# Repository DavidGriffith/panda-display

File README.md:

Panda Display Panel
===================

---

The Panda Display Panel is a hardware peripheral for use with the klh10 
pdp-10 emulator.  It was originally presented by Spare Time Gizmos.  
This one replaces the parallel port interface with a USB interface.

The original Panda Display Panel page is at 
http://www.sparetimegizmos.com/Hardware/Panda.htm

**Bill of Materials**

|Connectors| |
|:----------|---|
|J1| 1 x 4 0.1" header strip|
|J2| 2 x 3 0.1" header strip|
|U1| 28-pin narrow DIP socket|
|U2| 24-pin narrow DIP socket|

|Semiconductors| |
|:--------------|---|
|U1|		ATmega8 microcontroller -- 28-pin narrow DIP|
|U2|		Maxim MAX7219 matrix digit display driver -- 24-pin narrow DIP|
|D1,D2|		1N747 3.6V zener diodes|
|BAR1-BAR4|	10 segment LED bar display -- Lite-On LTA-1000HR|
|LED1-LED4|	Standard brightness red LED 5mm -- Kingbright WP1503ID|

|Crystals| |
|:--------|---|
|Y1|		16MHz quartz crystal -- HC49/US low profile|

|Resistors| |
|:---------|---|
|R1|		2.2K 0.25W 5%|
|R2|		4.7K 0.25W 5%|
|R3,R4|		68   0.25W 5%|
|R5|		10K  0.25W 5%|

|Capacitors| |
|:----------|---|
|C1|		10uF 25V electrolytic or tantalum|
|C2,C3|		0.1uF ceramic monolithic|
|C4,C5|		22pF ceramic monolithic|

**Assembly Notes**

Pay careful attention to the fact that the chips are mounted on the rear 
of the board and most of the passives are on the front.

1.  Mount the passive components first.  Make sure the leads are trimmed 
    so they won't interfere with the chip sockets.  The polarized 
    capacitor should be laid down on its side.
2.  Wash flux residue off the rear.  The chip sockets will make this 
    more difficult later.
3.  Mount the chip sockets and the header strips on the rear
4.  Mount the LED bars and the discrete LEDs on the front.

The discrete LEDs may be pressed up against the board unless you decide 
to mount the LED bars in sockets.  If you want to do that, first mount 
sockets and install the LED bars in the sockets.  Then insert a discrete 
LED and turn the Panda Display over such that the LED bars lie flat upon 
the table.  Let the discrete LED fall against the table.  Once you're 
satisfied that the discrete LED is level with the LED bars, solder the 
discrete LED in place.  Repeat for the other discrete LEDs.

To build and install the firmware, you must have the AVR-GCC development 
environment including compiler, binutilities, and libc 
(http://www.nongnu.org/avr-libc/) and AVRDUDE
(http://www.nongnu.org/avrdude/) installed.  Most if not all current 
distributions of Linux and BSD include packages for installing these.  
You will also need an AVR programming device supported by AVRDUDE.  A 
USBtinyISP (https://www.adafruit.com/products/46) is commonly-available, 
reliable, and inexpensive.

It's a good idea to add your programmer to your system's udev rules.  
For the USBtinyISP, see https://learn.adafruit.com/usbtinyisp/avrdude

**Mounting and Use**

The Panda Display is intended to be mounted in a 5.25" external drive 
bay behind a knockout panel.  It's up to you to make this as simply or 
elaborately as you desire.  An overlay may be applied over the top to 
dress it up.

This edition of the Panda Display is powered and driven through a USB 
port.  There are two ways of going about the cabling.  If you have a 
spare USB header on your computer's motherboard, you'll need to make up 
a four-conductor cable terminated at both ends with a 1x4 0.1" female 
header socket.

If you have a regular Type-A socket inside your computer, take an 
ordinary USB cable, cut off the Type-B end, trim the jacket, and crimp 
the conductors to a 1x4 0.1" female header socket.

Finally, to make any meaningful use of the Panda Display, you will need 
a PDP-10 emulator which has been patched to make use of it.  Since 
Kenneth L. Harrenstien's klh10 pdp-10 emulator was patched by Mark 
Crispin to use the original Panda Display, I chose to modify that to use 
this new Panda Display.  Get it here: 
https://github.com/DavidGriffith/klh10.

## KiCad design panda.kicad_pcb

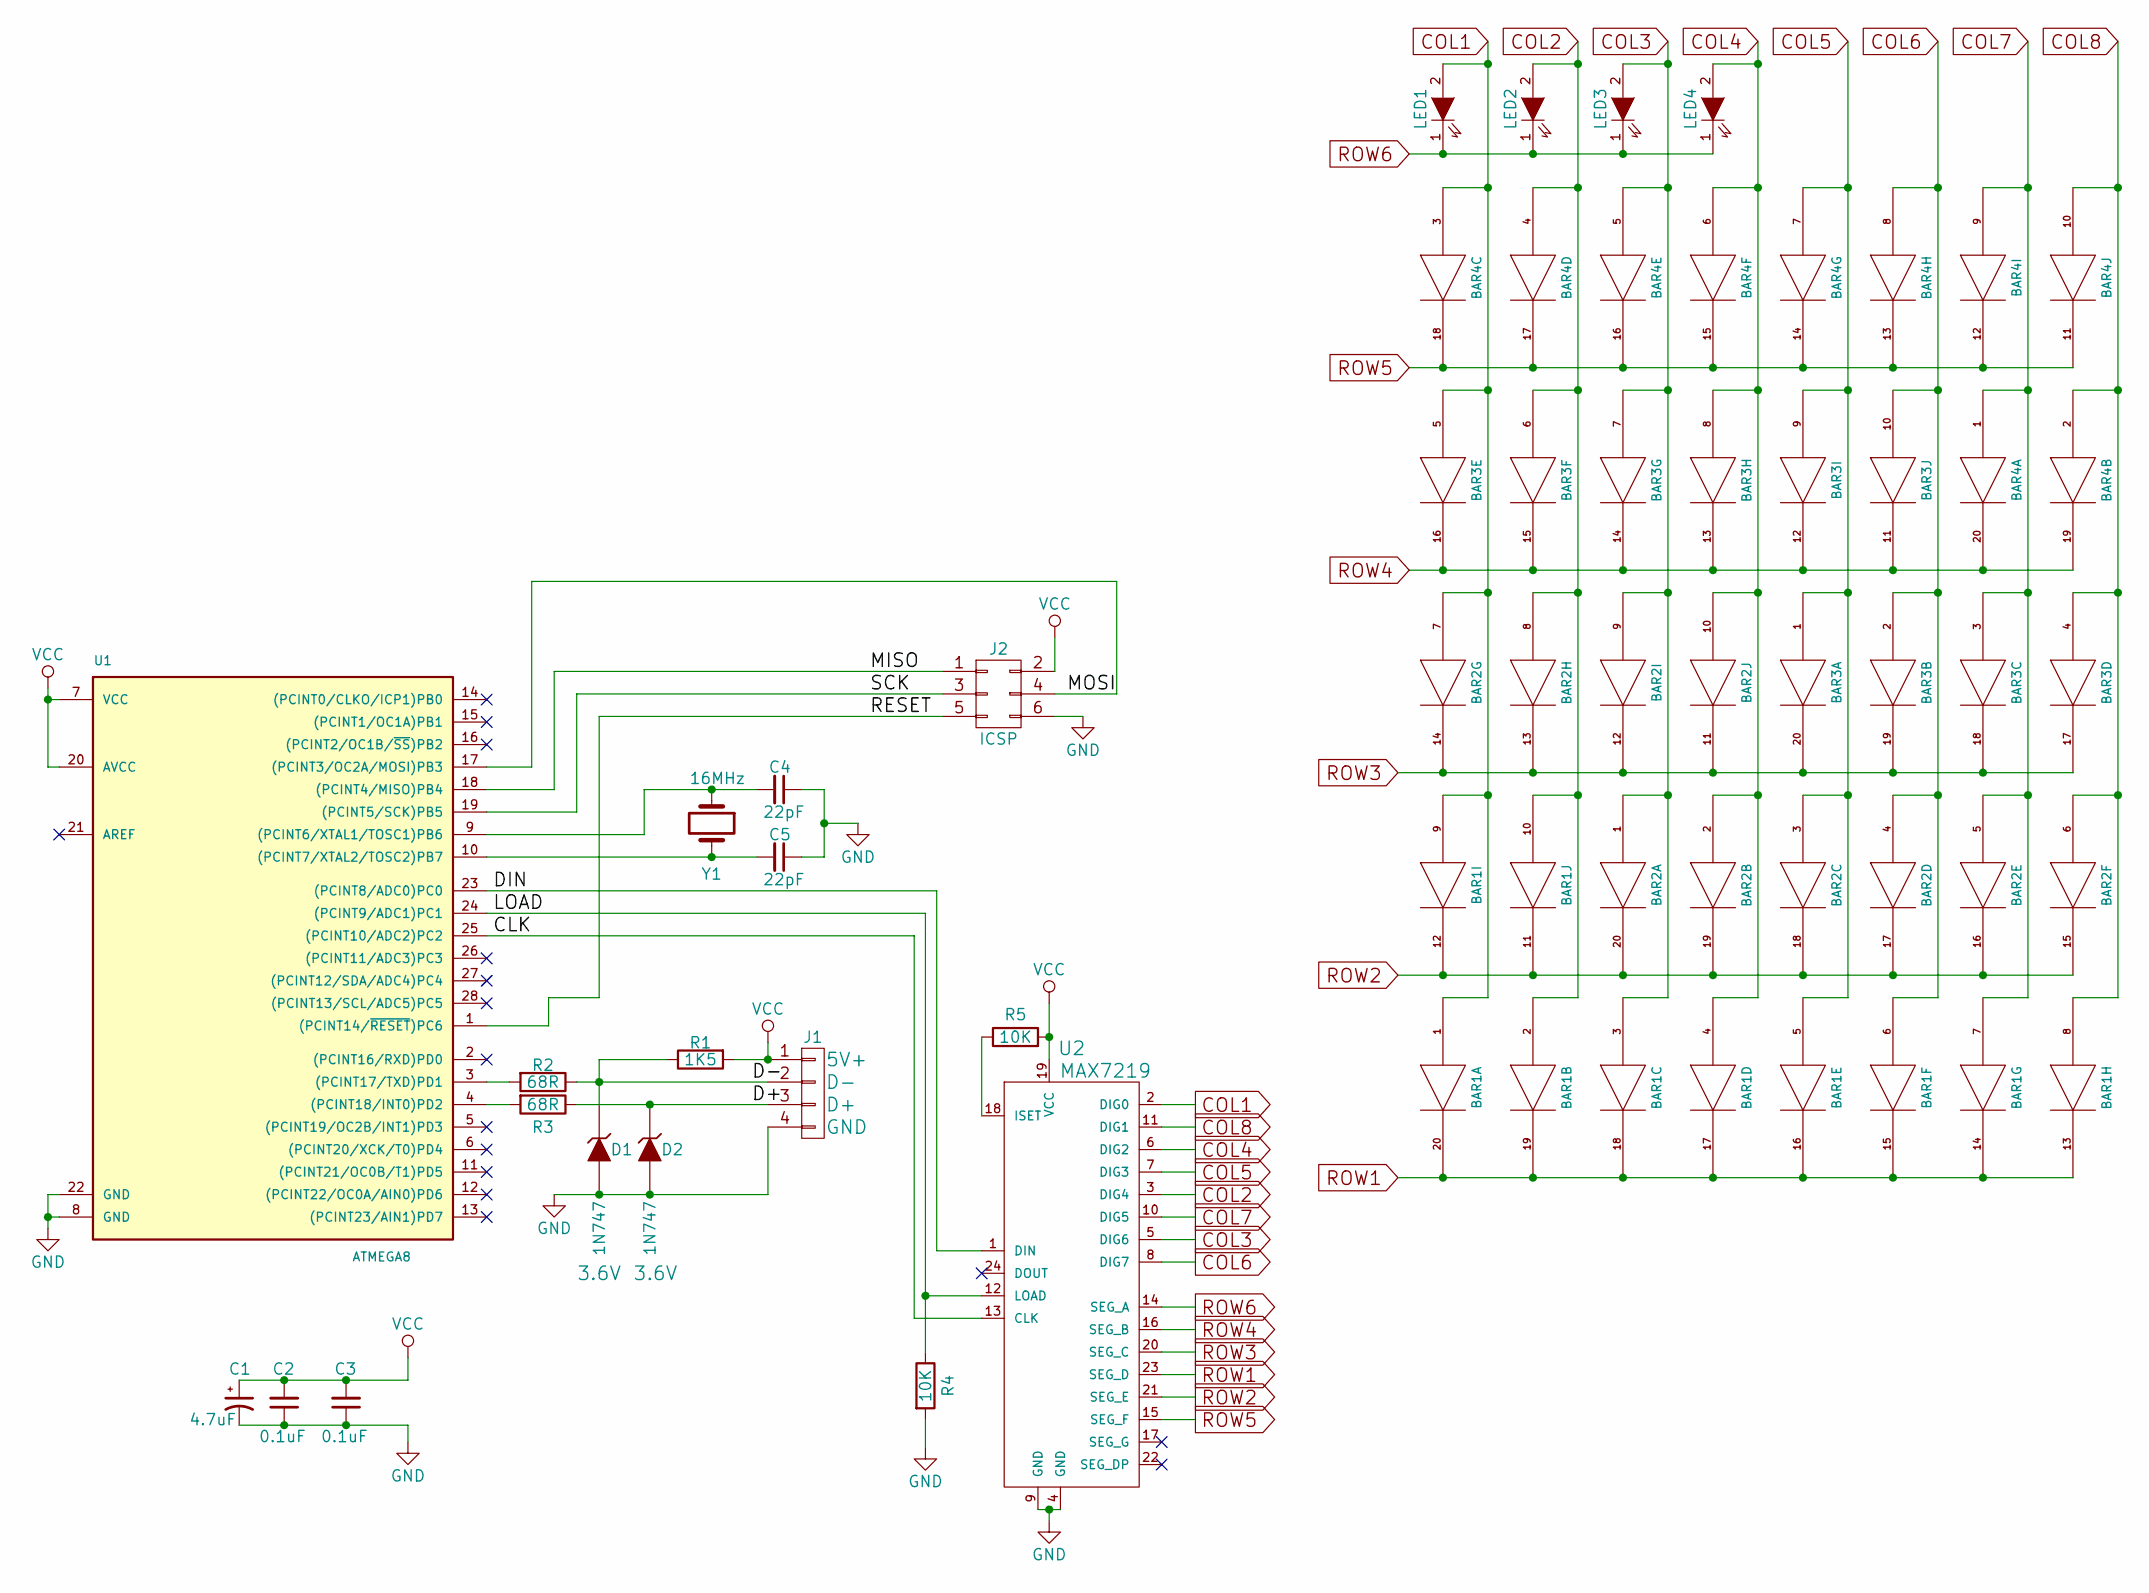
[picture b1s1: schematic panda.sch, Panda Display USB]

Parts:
BAR1, BAR2, BAR3, BAR4: DOT-BAR; DIP-20_W7.62mm
C1: 4.7uF; CP_Radial_D5.0mm_P2.50mm
C2, C3: 0.1uF; C_Disc_D3.0mm_W1.6mm_P2.50mm
C4, C5: 22pF; C_Disc_D3.0mm_W1.6mm_P2.50mm
D1, D2: 1N747; D_DO-35_SOD27_P7.62mm_Horizontal; Voltage 3.6V
J1: USB; Pin_Header_Straight_1x04_Pitch2.54mm
J2: ICSP; Pin_Header_Straight_2x03_Pitch2.54mm
LED1, LED2, LED3, LED4: LED; LED_D5.0mm
R1: 1K5; R_Axial_DIN0204_L3.6mm_D1.6mm_P7.62mm_Horizontal
R2, R3: 68R; R_Axial_DIN0204_L3.6mm_D1.6mm_P7.62mm_Horizontal
R4, R5: 10K; R_Axial_DIN0204_L3.6mm_D1.6mm_P7.62mm_Horizontal
U1: ATMEGA8; DIP-28_W7.62mm
U2: MAX7219; DIP-24_W7.62mm
Y1: 16MHz; Crystal_HC49-U_Vertical

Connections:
/CLK: U1.25 ((PCINT10/ADC2)PC2), U2.13 (CLK)
/D+: D2.1 (K), J1.3, R3.1
/D-: D1.1 (K), J1.2, R1.1, R2.1
/DIN: U1.23 ((PCINT8/ADC0)PC0), U2.1 (DIN)
/LOAD: R4.1, U1.24 ((PCINT9/ADC1)PC1), U2.12 (LOAD)
/MISO: J2.1, U1.18 ((PCINT4/MISO)PB4)
/MOSI: J2.4, U1.17 ((PCINT3/OC2A/MOSI)PB3)
/RESET: J2.5, U1.1 ((PCINT14/~RESET~)PC6)
/SCK: J2.3, U1.19 ((PCINT5/SCK)PB5)
COL1: BAR1.1 (A), BAR1.9 (A), BAR2.7 (A), BAR3.5 (A), BAR4.3 (A), LED1.2 (A), U2.2 (DIG0)
COL2: BAR1.2 (A), BAR1.10 (A), BAR2.8 (A), BAR3.6 (A), BAR4.4 (A), LED2.2 (A), U2.3 (DIG4)
COL3: BAR1.3 (A), BAR2.1 (A), BAR2.9 (A), BAR3.7 (A), BAR4.5 (A), LED3.2 (A), U2.5 (DIG6)
COL4: BAR1.4 (A), BAR2.2 (A), BAR2.10 (A), BAR3.8 (A), BAR4.6 (A), LED4.2 (A), U2.6 (DIG2)
COL5: BAR1.5 (A), BAR2.3 (A), BAR3.1 (A), BAR3.9 (A), BAR4.7 (A), U2.7 (DIG3)
COL6: BAR1.6 (A), BAR2.4 (A), BAR3.2 (A), BAR3.10 (A), BAR4.8 (A), U2.8 (DIG7)
COL7: BAR1.7 (A), BAR2.5 (A), BAR3.3 (A), BAR4.1 (A), BAR4.9 (A), U2.10 (DIG5)
COL8: BAR1.8 (A), BAR2.6 (A), BAR3.4 (A), BAR4.2 (A), BAR4.10 (A), U2.11 (DIG1)
GND: C1.2, C2.1, C3.1, C4.1, C5.1, D1.2 (A), D2.2 (A), J1.4, J2.6, R4.2, U1.8 (GND), U1.22 (GND), U2.4 (GND), U2.9 (GND)
unnamed: C4.2, U1.9 ((PCINT6/XTAL1/TOSC1)PB6), Y1.1
unnamed: C5.2, U1.10 ((PCINT7/XTAL2/TOSC2)PB7), Y1.2
unnamed: R2.2, U1.3 ((PCINT17/TXD)PD1)
unnamed: R3.2, U1.4 ((PCINT18/INT0)PD2)
unnamed: R5.1, U2.18 (ISET)
ROW1: BAR1.13 (K), BAR1.14 (K), BAR1.15 (K), BAR1.16 (K), BAR1.17 (K), BAR1.18 (K), BAR1.19 (K), BAR1.20 (K), U2.23 (SEG_D)
ROW2: BAR1.11 (K), BAR1.12 (K), BAR2.15 (K), BAR2.16 (K), BAR2.17 (K), BAR2.18 (K), BAR2.19 (K), BAR2.20 (K), U2.21 (SEG_E)
ROW3: BAR2.11 (K), BAR2.12 (K), BAR2.13 (K), BAR2.14 (K), BAR3.17 (K), BAR3.18 (K), BAR3.19 (K), BAR3.20 (K), U2.20 (SEG_C)
ROW4: BAR3.11 (K), BAR3.12 (K), BAR3.13 (K), BAR3.14 (K), BAR3.15 (K), BAR3.16 (K), BAR4.19 (K), BAR4.20 (K), U2.16 (SEG_B)
ROW5: BAR4.11 (K), BAR4.12 (K), BAR4.13 (K), BAR4.14 (K), BAR4.15 (K), BAR4.16 (K), BAR4.17 (K), BAR4.18 (K), U2.15 (SEG_F)
ROW6: LED1.1 (K), LED2.1 (K), LED3.1 (K), LED4.1 (K), U2.14 (SEG_A)
VCC: C1.1, C2.2, C3.2, J1.1, J2.2, R1.2, R5.2, U1.7 (VCC), U1.20 (AVCC), U2.19 (VCC)

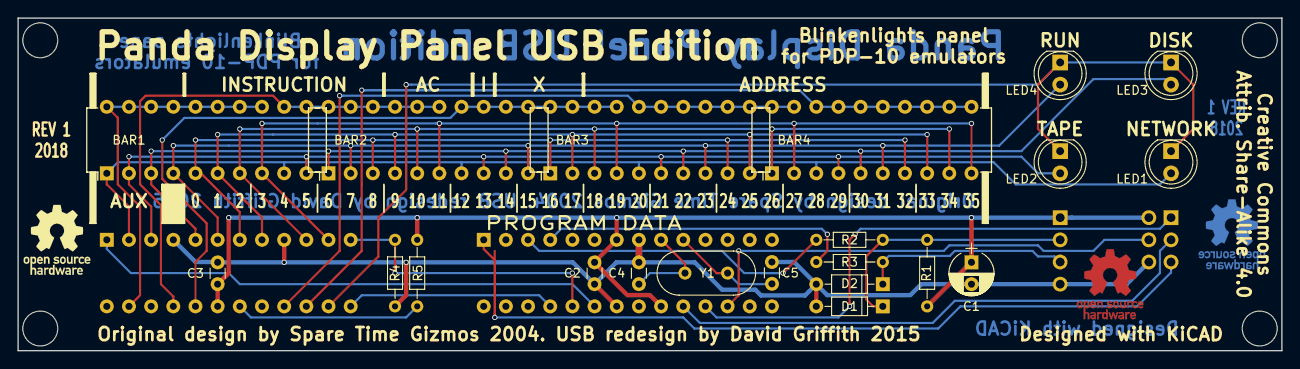
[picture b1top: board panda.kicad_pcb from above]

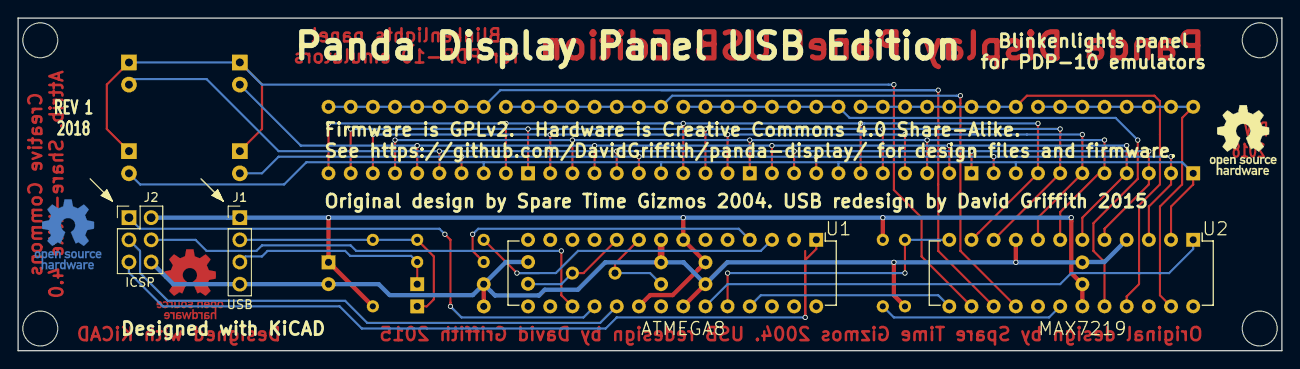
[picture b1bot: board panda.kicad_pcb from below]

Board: 2 copper layers, 144.8 x 38.1 mm, 25 parts (4 on the bottom side), 30 nets.

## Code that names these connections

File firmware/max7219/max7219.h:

/*
max7219 lib 0x01

copyright (c) Davide Gironi, 2013

Released under GPLv3.
Please refer to LICENSE file for licensing information.
*/


#ifndef MAX7219_H_
#define MAX7219_H_

#include <avr/io.h>


//setup ports
/*
#define MAX7219_DINDDR DDRD
#define MAX7219_DINPORT PORTD
#define MAX7219_DININPUT PD2
#define MAX7219_CLKDDR DDRD
#define MAX7219_CLKPORT PORTD
#define MAX7219_CLKINPUT PD3
#define MAX7219_LOADDDR DDRD
#define MAX7219_LOADPORT PORTD
#define MAX7219_LOADINPUT PD4
*/

#define MAX7219_DINDDR DDRC
#define MAX7219_DINPORT PORTC
#define MAX7219_DININPUT PC0

#define MAX7219_CLKDDR DDRC
#define MAX7219_CLKPORT PORTC
#define MAX7219_CLKINPUT PC2

#define MAX7219_LOADDDR DDRC
#define MAX7219_LOADPORT PORTC
#define MAX7219_LOADINPUT PC1

//setup number of chip attached to the board
//#define MAX7219_ICNUMBER 2
#define MAX7219_ICNUMBER 1

//define registers
#define MAX7218_REGNOOP 0x00
#define MAX7218_REGDIGIT0 0x01
#define MAX7218_REGDIGIT1 0x02
#define MAX7218_REGDIGIT2 0x03
#define MAX7218_REGDIGIT3 0x04
#define MAX7218_REGDIGIT4 0x05
#define MAX7218_REGDIGIT5 0x06
#define MAX7218_REGDIGIT6 0x07
#define MAX7218_REGDIGIT7 0x08
#define MAX7218_REGDECODE 0x09
#define MAX7218_REGINTENSITY 0x0A
#define MAX7218_REGSCANLIMIT 0x0B
#define MAX7218_REGSHUTDOWN 0x0C
#define MAX7218_REGTEST 0x0F


//functions
extern void max7219_send(uint8_t icnum, uint8_t reg, uint8_t data);
extern void max7219_shutdown(uint8_t icnum, uint8_t value);
extern void max7219_intensity(uint8_t icnum, uint8_t value);
extern void max7219_test(uint8_t icnum, uint8_t value);
extern void max7219_scanlimit(uint8_t icnum, uint8_t value);
extern void max7219_decode(uint8_t icnum, uint8_t value);
extern void max7219_digit0(uint8_t icnum, uint8_t value);
extern void max7219_digit1(uint8_t icnum, uint8_t value);
extern void max7219_digit2(uint8_t icnum, uint8_t value);
extern void max7219_digit3(uint8_t icnum, uint8_t value);
extern void max7219_digit4(uint8_t icnum, uint8_t value);
extern void max7219_digit5(uint8_t icnum, uint8_t value);
extern void max7219_digit6(uint8_t icnum, uint8_t value);
extern void max7219_digit7(uint8_t icnum, uint8_t value);
extern void max7219_digit(uint8_t icnum, uint8_t digit, uint8_t value);
extern void max7219_init();

#endif

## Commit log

2015-11-19 Initial commit.
2015-11-25 Move chips and polarized capacitor to other side. Makes for easier socketing.
2015-11-25 Fixed up 3d models.
2015-11-25 Variant with two rows of LED bars.
2015-11-25 Move chips and some other stuff to the back.
2015-12-02 Add voltage labels to zener diodes.
2015-12-05 Cleanup and wording.
2015-12-05 Add BOM and assembly and use notes.
2015-12-05 Enlarge vias and added blurbs.
2015-12-05 Added 3d renderings.
2015-12-05 Minor aesthetic tweak.
2015-12-05 Even more tweaks.
2015-12-08 Update and tweak.
2015-12-08 Added 3d renders.
2015-12-08 Add BOM and notes to README.md.
2015-12-08 Reduce height of crystal.
2015-12-08 Tweak board and update 3d renders.
2015-12-26 Slight mods to accomodate firmware.
2015-12-26 Initial commit of firmware.
2015-12-26 Typos and tweaks to README.md
2015-12-30 Added host side test program.
2016-01-02 Cleaner USB stuff.
2016-01-03 Moving D- pin around in firmware.
2016-01-03 Adding PDF of schematics for convenient browsing.
2016-01-19 Update 3D renders.
2016-01-25 Update tweaks.
2016-02-06 Final tweaks.
2016-02-06 3d rendering tweaks.
2016-02-17 Update PDF schematics.
2016-02-21 Tweak value of polarized cap.
2016-02-21 Shift OSH logo down to avoid hitting the LED3's column trace.
2016-02-25 Rework firmware to make more sense on the host end.
    It turns out that the board with a MAX7219 and an 8x8 LED matrix I was
    using for testing has a funky pinout which doesn't match how the Panda
    Display is wired. Pin 1 does not correspond to column 1 and so on. Then
    I discovered that I wired the board such that I need to rotate the
    bitmap 90 degrees clockwise. I could possibly rework the board design
    to save time in the microcontroller. Maybe it's not necessary,
2016-02-26 Rewrote assembly notes.
2016-02-26 Link to Adafruit's USBtinyISP page.
2016-03-10 Update with link to klh10 with my modifications.
2016-05-12 Added demo program for pdp10.
    Obtained from Jan deRie who used it to produce this video of an
    original parallel port Panda Display doing its thing:
    https://www.youtube.com/watch?v=g_LcQ5apODg
2018-05-17 Added 3D model from http://smisioto.no-ip.org/elettronica/kicad/kicad-en.htm
2018-05-17 More 3D models from http://smisioto.no-ip.org/elettronica/kicad/kicad-en.htm
    Socketed DIPs.
2018-05-17 Clean up lots of messiness.
2018-05-17 Moved around silks. Added helpful legends.
2018-05-18 Scoot chips down a bit to make room for nicer looking Program Data legends.
2018-05-18 Update 3D board renders.
2018-05-18 Cleanup Makefile for firmware. panda-display.c makes more sense than main.c.
2018-05-18 Add copper layer to revision marking.
2018-05-18 Add legends to descrete LEDs. Fix the disk LED's 3D rendering elevation.
2018-05-18 Move around copper layer Open Source Hardware logos.
2018-05-18 Update 3D renders and add renders of the bare board.

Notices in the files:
panda.kicad_pcb:
Firmware is GPLv2.  Hardware is Creative Commons 4.0 Share-Alike.
